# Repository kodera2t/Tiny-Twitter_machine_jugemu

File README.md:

This is a tiny twitter machine, named "Jugemu", after famous Japanese old "rakugo".
One FlashAir (Toshiba) and several components consisting "fixed sentence twitter machine".
The function is simple. four switches are arranged on PCB, and pushing one of them, corresponding sentence will be sent to Twitter.
This simple program is released under GPL v2.
# Tiny-Twitter_machine_jugemu

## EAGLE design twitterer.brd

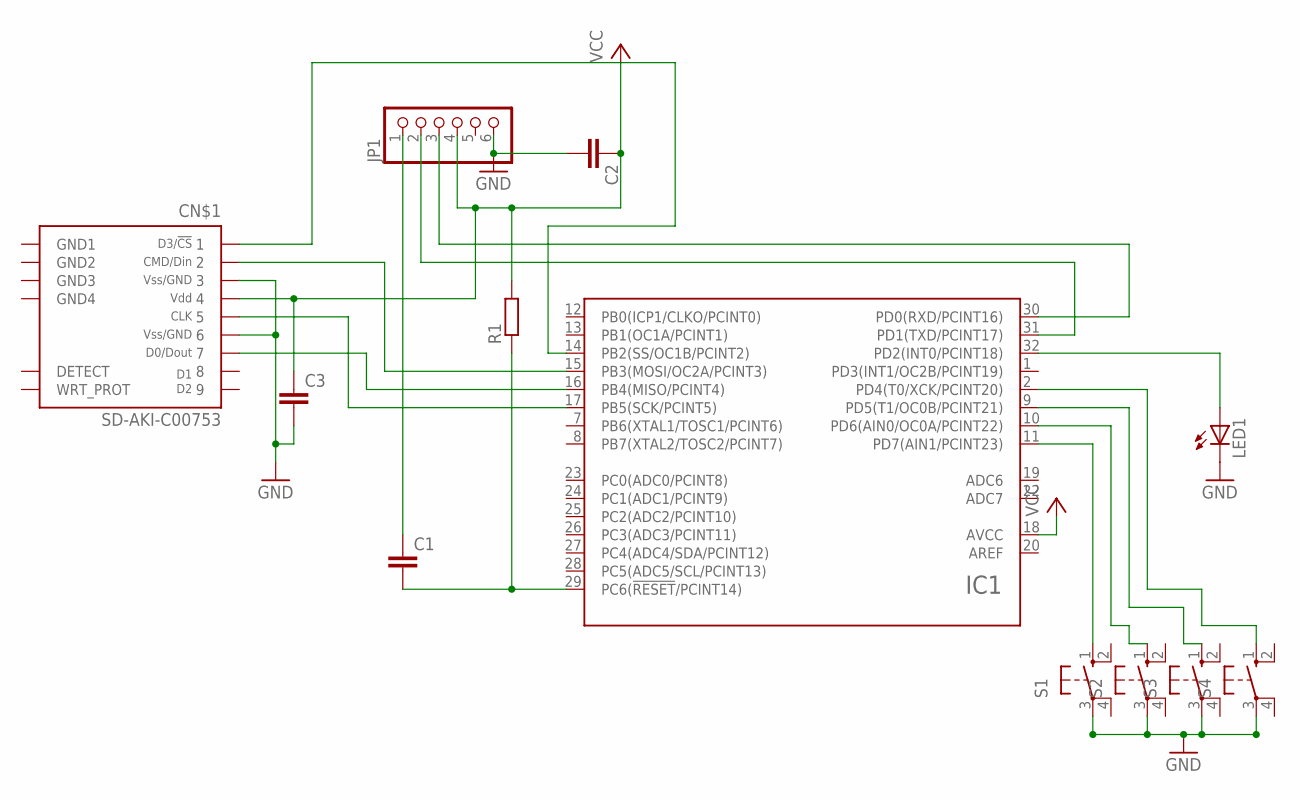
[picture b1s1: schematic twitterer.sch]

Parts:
C1, C2, C3: CC0603; C0603
CN$1: SD-AKI-C00753; C-1734234
IC1: ATMEGA48/88/168/328-AU; TQFP32-08
JP1: PINHD-1X6; 1X06
LED1: LED_ELD260; LED_LD260
R1: RR0603; R0603
S1, S2, S3, S4: 10-XX; B3F-10XX

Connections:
GND: C2.2, C3.2, CN$1.3, CN$1.6, IC1.3 (GND), IC1.5 (GND), IC1.21 (GND), JP1.6, LED1.K (C), S1.3, S2.3, S3.3, S4.3
GND1: CN$1.GND1
GND2: CN$1.GND2
GND3: CN$1.GND3
GND4: CN$1.GND4
unnamed: C1.1, JP1.1
unnamed: C1.2, IC1.29 (PC6(!RESET!/PCINT14)), R1.1
unnamed: IC1.31 (PD1(TXD/PCINT17)), JP1.2
unnamed: IC1.30 (PD0(RXD/PCINT16)), JP1.3
unnamed: CN$1.1, IC1.14 (PB2(SS/OC1B/PCINT2))
unnamed: CN$1.2, IC1.15 (PB3(MOSI/OC2A/PCINT3))
unnamed: CN$1.7, IC1.16 (PB4(MISO/PCINT4))
unnamed: CN$1.5, IC1.17 (PB5(SCK/PCINT5))
unnamed: IC1.32 (PD2(INT0/PCINT18)), LED1.A
unnamed: IC1.11 (PD7(AIN1/PCINT23)), S1.1 (S)
unnamed: IC1.10 (PD6(AIN0/OC0A/PCINT22)), S2.1 (S)
unnamed: IC1.9 (PD5(T1/OC0B/PCINT21)), S3.1 (S)
unnamed: IC1.2 (PD4(T0/XCK/PCINT20)), S4.1 (S)
VCC: C2.1, C3.1, CN$1.4, IC1.4 (UCC), IC1.6 (UCC), IC1.18 (AVCC), JP1.4, R1.2

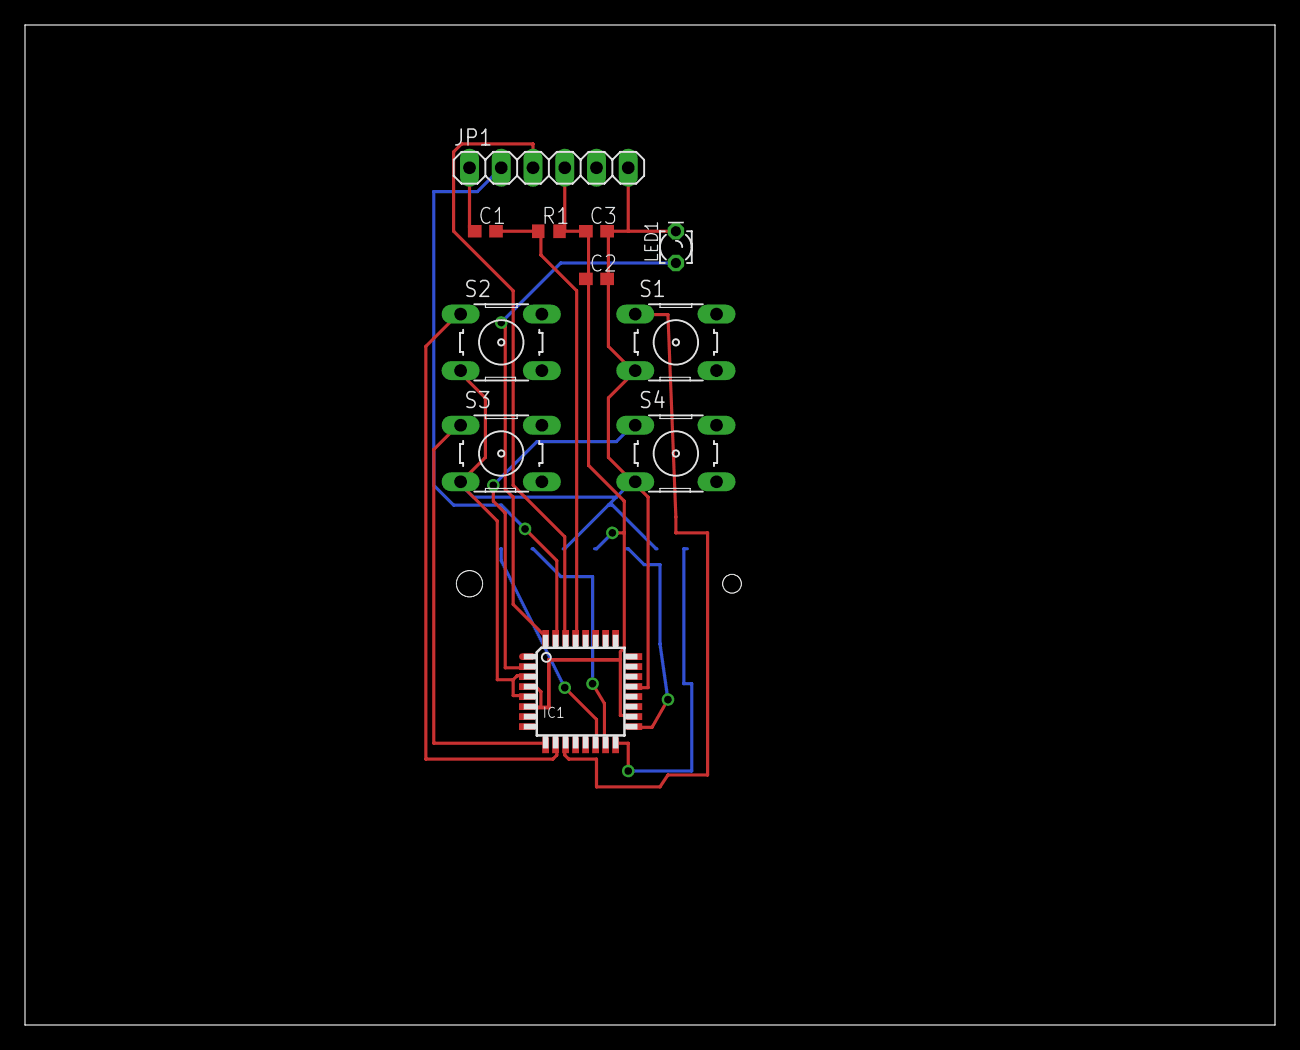
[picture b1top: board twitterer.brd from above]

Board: 2 copper layers, 100.0 x 80.0 mm, 12 parts (1 on the bottom side), 15 nets.

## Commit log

2015-03-11 Initial submission
